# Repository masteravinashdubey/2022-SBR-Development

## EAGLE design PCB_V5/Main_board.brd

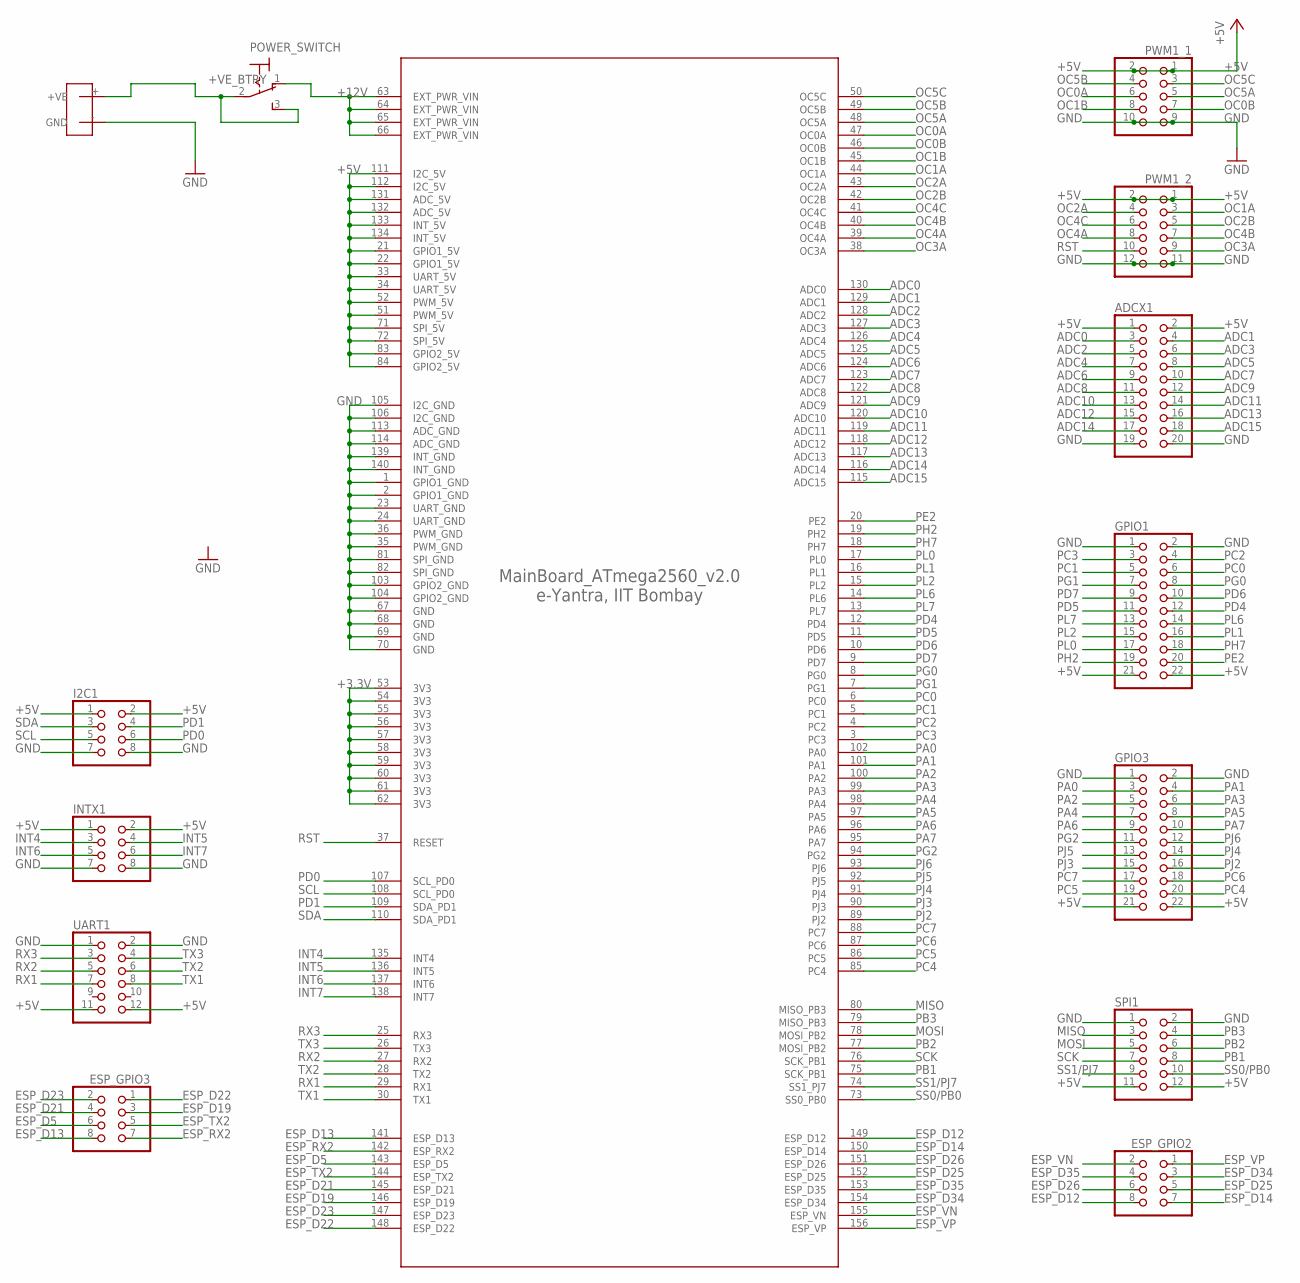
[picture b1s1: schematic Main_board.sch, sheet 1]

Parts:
ADCX1: PINHD-2X10; 2X10
ESP_GPIO2, ESP_GPIO3: PINHD-2X4; 2X04
EYFI_MEGA: ATMEGA2560_V2.0
GPIO1, GPIO3: PINHD-2X11; 2X11
I2C1: PINHD-2X4; 2X04
INTX1: PINHD-2X4; 2X04
POWER_SWITCH: M9040P
PWM1_1: PINHD-2X5; 2X05
PWM1_2: PINHD-2X6; 2X06
SPI1: PINHD-2X6; 2X06
U$1: DEANS
UART1: PINHD-2X6; 2X06

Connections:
+3.3V: EYFI_MEGA.53 (3V3), EYFI_MEGA.54 (3V3), EYFI_MEGA.55 (3V3), EYFI_MEGA.56 (3V3), EYFI_MEGA.57 (3V3), EYFI_MEGA.58 (3V3), EYFI_MEGA.59 (3V3), EYFI_MEGA.60 (3V3), EYFI_MEGA.61 (3V3), EYFI_MEGA.62 (3V3); also elsewhere on the board
+5V: ADCX1.1, ADCX1.2, EYFI_MEGA.21 (GPIO1_5V), EYFI_MEGA.22 (GPIO1_5V), EYFI_MEGA.33 (UART_5V), EYFI_MEGA.34 (UART_5V), EYFI_MEGA.51 (PWM_5V), EYFI_MEGA.52 (PWM_5V), EYFI_MEGA.71 (SPI_5V), EYFI_MEGA.72 (SPI_5V), EYFI_MEGA.83 (GPIO2_5V), EYFI_MEGA.84 (GPIO2_5V), EYFI_MEGA.111 (I2C_5V), EYFI_MEGA.112 (I2C_5V), EYFI_MEGA.131 (ADC_5V), EYFI_MEGA.132 (ADC_5V), EYFI_MEGA.133 (INT_5V), EYFI_MEGA.134 (INT_5V), GPIO1.21, GPIO1.22, GPIO3.21, GPIO3.22, I2C1.1, I2C1.2, INTX1.1, INTX1.2, PWM1_1.1, PWM1_1.2, PWM1_2.1, PWM1_2.2, SPI1.11, SPI1.12, UART1.11, UART1.12; also elsewhere on the board
+12V: EYFI_MEGA.63 (EXT_PWR_VIN), EYFI_MEGA.64 (EXT_PWR_VIN), EYFI_MEGA.65 (EXT_PWR_VIN), EYFI_MEGA.66 (EXT_PWR_VIN), POWER_SWITCH.1 (O); also elsewhere on the board
+VE_BTRY: POWER_SWITCH.2, POWER_SWITCH.3 (S), U$1.+ (+VE)
ADC0: ADCX1.3, EYFI_MEGA.130 (ADC0); also elsewhere on the board
ADC1: ADCX1.4, EYFI_MEGA.129 (ADC1); also elsewhere on the board
ADC2: ADCX1.5, EYFI_MEGA.128 (ADC2); also elsewhere on the board
ADC3: ADCX1.6, EYFI_MEGA.127 (ADC3); also elsewhere on the board
ADC4: ADCX1.7, EYFI_MEGA.126 (ADC4)
ADC5: ADCX1.8, EYFI_MEGA.125 (ADC5)
ADC6: ADCX1.9, EYFI_MEGA.124 (ADC6)
ADC7: ADCX1.10, EYFI_MEGA.123 (ADC7)
ADC8: ADCX1.11, EYFI_MEGA.122 (ADC8)
ADC9: ADCX1.12, EYFI_MEGA.121 (ADC9)
ADC10: ADCX1.13, EYFI_MEGA.120 (ADC10)
ADC11: ADCX1.14, EYFI_MEGA.119 (ADC11)
ADC12: ADCX1.15, EYFI_MEGA.118 (ADC12); also elsewhere on the board
ADC13: ADCX1.16, EYFI_MEGA.117 (ADC13); also elsewhere on the board
ADC14: ADCX1.17, EYFI_MEGA.116 (ADC14); also elsewhere on the board
ADC15: ADCX1.18, EYFI_MEGA.115 (ADC15); also elsewhere on the board
ESP_D5: ESP_GPIO3.6, EYFI_MEGA.143 (ESP_D5)
ESP_D12: ESP_GPIO2.8, EYFI_MEGA.149 (ESP_D12)
ESP_D13: ESP_GPIO3.8, EYFI_MEGA.141 (ESP_D13)
ESP_D14: ESP_GPIO2.7, EYFI_MEGA.150 (ESP_D14)
ESP_D19: ESP_GPIO3.3, EYFI_MEGA.146 (ESP_D19)
ESP_D21: ESP_GPIO3.4, EYFI_MEGA.145 (ESP_D21)
ESP_D22: ESP_GPIO3.1, EYFI_MEGA.148 (ESP_D22)
ESP_D23: ESP_GPIO3.2, EYFI_MEGA.147 (ESP_D23)
ESP_D25: ESP_GPIO2.5, EYFI_MEGA.152 (ESP_D25)
ESP_D26: ESP_GPIO2.6, EYFI_MEGA.151 (ESP_D26)
ESP_D34: ESP_GPIO2.3, EYFI_MEGA.154 (ESP_D34)
ESP_D35: ESP_GPIO2.4, EYFI_MEGA.153 (ESP_D35)
ESP_RX2: ESP_GPIO3.7, EYFI_MEGA.142 (ESP_RX2)
ESP_TX2: ESP_GPIO3.5, EYFI_MEGA.144 (ESP_TX2)
ESP_VN: ESP_GPIO2.2, EYFI_MEGA.155 (ESP_VN)
ESP_VP: ESP_GPIO2.1, EYFI_MEGA.156 (ESP_VP)
GND: ADCX1.19, ADCX1.20, EYFI_MEGA.1 (GPIO1_GND), EYFI_MEGA.2 (GPIO1_GND), EYFI_MEGA.23 (UART_GND), EYFI_MEGA.24 (UART_GND), EYFI_MEGA.35 (PWM_GND), EYFI_MEGA.36 (PWM_GND), EYFI_MEGA.67 (GND), EYFI_MEGA.68 (GND), EYFI_MEGA.69 (GND), EYFI_MEGA.70 (GND), EYFI_MEGA.81 (SPI_GND), EYFI_MEGA.82 (SPI_GND), EYFI_MEGA.103 (GPIO2_GND), EYFI_MEGA.104 (GPIO2_GND), EYFI_MEGA.105 (I2C_GND), EYFI_MEGA.106 (I2C_GND), EYFI_MEGA.113 (ADC_GND), EYFI_MEGA.114 (ADC_GND), EYFI_MEGA.139 (INT_GND), EYFI_MEGA.140 (INT_GND), GPIO1.1, GPIO1.2, GPIO3.1, GPIO3.2, I2C1.7, I2C1.8, INTX1.7, INTX1.8, PWM1_1.9, PWM1_1.10, PWM1_2.11, PWM1_2.12, SPI1.1, SPI1.2, U$1.- (GND), UART1.1, UART1.2; also elsewhere on the board
INT4: EYFI_MEGA.135 (INT4), INTX1.3; also elsewhere on the board
INT5: EYFI_MEGA.136 (INT5), INTX1.4; also elsewhere on the board
INT6: EYFI_MEGA.137 (INT6), INTX1.5; also elsewhere on the board
INT7: EYFI_MEGA.138 (INT7), INTX1.6; also elsewhere on the board
MISO: EYFI_MEGA.80 (MISO_PB3), SPI1.3
MOSI: EYFI_MEGA.78 (MOSI_PB2), SPI1.5
OC0A: EYFI_MEGA.47 (OC0A), PWM1_1.6
OC0B: EYFI_MEGA.46 (OC0B), PWM1_1.7
OC1A: EYFI_MEGA.44 (OC1A), PWM1_2.3
OC1B: EYFI_MEGA.45 (OC1B), PWM1_1.8; also elsewhere on the board
OC2A: EYFI_MEGA.43 (OC2A), PWM1_2.4
OC2B: EYFI_MEGA.42 (OC2B), PWM1_2.5; also elsewhere on the board
OC3A: EYFI_MEGA.38 (OC3A), PWM1_2.9; also elsewhere on the board
OC4A: EYFI_MEGA.39 (OC4A), PWM1_2.8; also elsewhere on the board
OC4B: EYFI_MEGA.40 (OC4B), PWM1_2.7; also elsewhere on the board
OC4C: EYFI_MEGA.41 (OC4C), PWM1_2.6; also elsewhere on the board
OC5A: EYFI_MEGA.48 (OC5A), PWM1_1.5; also elsewhere on the board
OC5B: EYFI_MEGA.49 (OC5B), PWM1_1.4; also elsewhere on the board
OC5C: EYFI_MEGA.50 (OC5C), PWM1_1.3
PA0: EYFI_MEGA.102 (PA0), GPIO3.3; also elsewhere on the board
PA1: EYFI_MEGA.101 (PA1), GPIO3.4; also elsewhere on the board
PA2: EYFI_MEGA.100 (PA2), GPIO3.5; also elsewhere on the board
PA3: EYFI_MEGA.99 (PA3), GPIO3.6; also elsewhere on the board
PA4: EYFI_MEGA.98 (PA4), GPIO3.7; also elsewhere on the board
PA5: EYFI_MEGA.97 (PA5), GPIO3.8; also elsewhere on the board
PA6: EYFI_MEGA.96 (PA6), GPIO3.9; also elsewhere on the board
PA7: EYFI_MEGA.95 (PA7), GPIO3.10; also elsewhere on the board
PB1: EYFI_MEGA.75 (SCK_PB1), SPI1.8
PB2: EYFI_MEGA.77 (MOSI_PB2), SPI1.6
PB3: EYFI_MEGA.79 (MISO_PB3), SPI1.4
PC0: EYFI_MEGA.6 (PC0), GPIO1.6; also elsewhere on the board
PC1: EYFI_MEGA.5 (PC1), GPIO1.5; also elsewhere on the board
PC2: EYFI_MEGA.4 (PC2), GPIO1.4; also elsewhere on the board
PC3: EYFI_MEGA.3 (PC3), GPIO1.3; also elsewhere on the board
PC4: EYFI_MEGA.85 (PC4), GPIO3.20; also elsewhere on the board
PC5: EYFI_MEGA.86 (PC5), GPIO3.19; also elsewhere on the board
PC6: EYFI_MEGA.87 (PC6), GPIO3.18; also elsewhere on the board
PC7: EYFI_MEGA.88 (PC7), GPIO3.17; also elsewhere on the board
PD0: EYFI_MEGA.107 (SCL_PD0), I2C1.6
PD1: EYFI_MEGA.109 (SDA_PD1), I2C1.4
PD4: EYFI_MEGA.12 (PD4), GPIO1.12; also elsewhere on the board
PD5: EYFI_MEGA.11 (PD5), GPIO1.11; also elsewhere on the board
PD6: EYFI_MEGA.10 (PD6), GPIO1.10; also elsewhere on the board
PD7: EYFI_MEGA.9 (PD7), GPIO1.9; also elsewhere on the board
PE2: EYFI_MEGA.20 (PE2), GPIO1.20
PG0: EYFI_MEGA.8 (PG0), GPIO1.8
PG1: EYFI_MEGA.7 (PG1), GPIO1.7
PG2: EYFI_MEGA.94 (PG2), GPIO3.11; also elsewhere on the board
PH2: EYFI_MEGA.19 (PH2), GPIO1.19
PH7: EYFI_MEGA.18 (PH7), GPIO1.18
PJ2: EYFI_MEGA.89 (PJ2), GPIO3.16
PJ3: EYFI_MEGA.90 (PJ3), GPIO3.15
PJ4: EYFI_MEGA.91 (PJ4), GPIO3.14
PJ5: EYFI_MEGA.92 (PJ5), GPIO3.13
PJ6: EYFI_MEGA.93 (PJ6), GPIO3.12; also elsewhere on the board
PL0: EYFI_MEGA.17 (PL0), GPIO1.17
PL1: EYFI_MEGA.16 (PL1), GPIO1.16
PL2: EYFI_MEGA.15 (PL2), GPIO1.15
PL6: EYFI_MEGA.14 (PL6), GPIO1.14
PL7: EYFI_MEGA.13 (PL7), GPIO1.13
RST: EYFI_MEGA.37 (RESET), PWM1_2.10
RX1: EYFI_MEGA.29 (RX1), UART1.7; also elsewhere on the board
RX2: EYFI_MEGA.27 (RX2), UART1.5
RX3: EYFI_MEGA.25 (RX3), UART1.3
SCK: EYFI_MEGA.76 (SCK_PB1), SPI1.7
SCL: EYFI_MEGA.108 (SCL_PD0), I2C1.5; also elsewhere on the board
SDA: EYFI_MEGA.110 (SDA_PD1), I2C1.3; also elsewhere on the board
SS0/PB0: EYFI_MEGA.73 (SS0_PB0), SPI1.10
SS1/PJ7: EYFI_MEGA.74 (SS1_PJ7), SPI1.9
TX1: EYFI_MEGA.30 (TX1), UART1.8
TX2: EYFI_MEGA.28 (TX2), UART1.6
TX3: EYFI_MEGA.26 (TX3), UART1.4

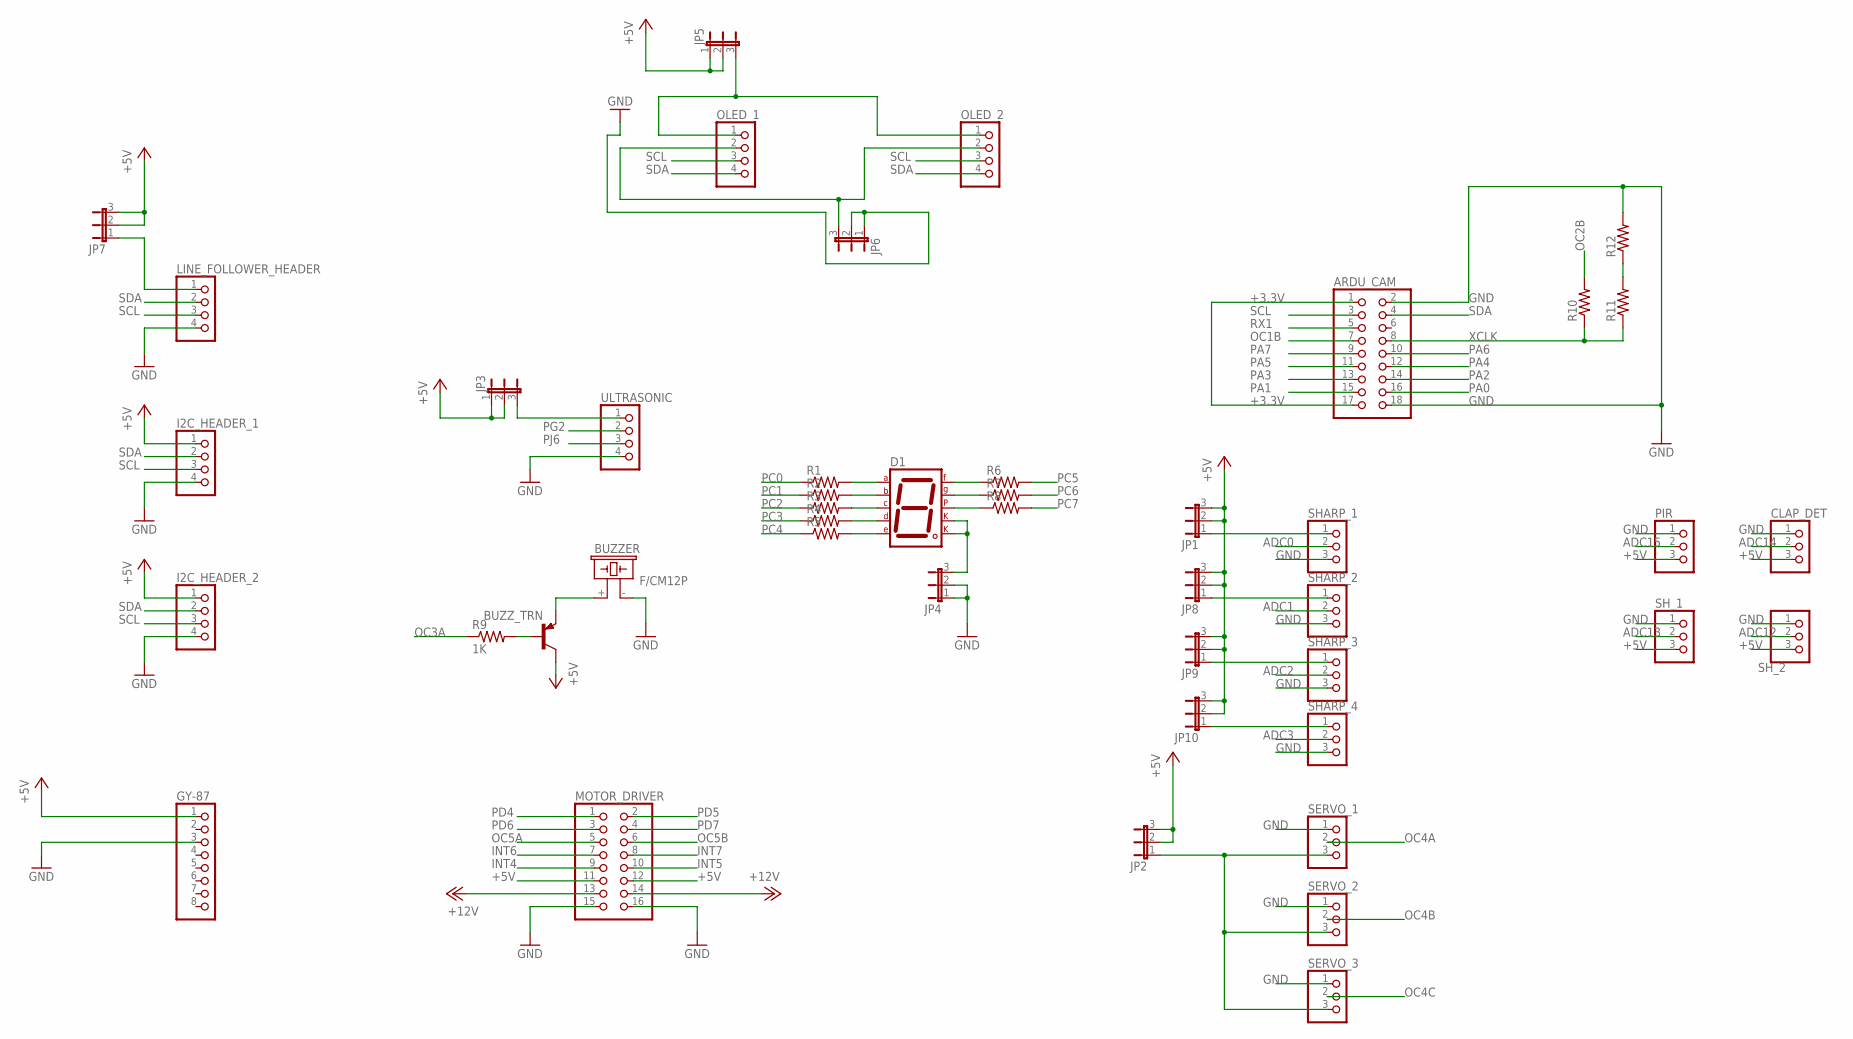
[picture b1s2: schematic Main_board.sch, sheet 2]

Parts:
ARDU_CAM: PINHD-2X9; 2X09
BUZZER: F/CM12P
BUZZ_TRN: BC807-16-PNP-SOT23-BEC; SOT23-BEC
CLAP_DET: PINHD-1X3; 1X03
D1: 7SEG-CK; 7SEG-13
GY-87: PINHD-1X8; 1X08
I2C_HEADER_1, I2C_HEADER_2: PINHD-1X4; 1X04
JP1, JP2, JP3, JP4, JP5, JP6, JP7, JP8, JP9, JP10: JP2E; JP2
LINE_FOLLOWER_HEADER: PINHD-1X4; 1X04
MOTOR_DRIVER: PINHD-2X8; 2X08
OLED_1, OLED_2: PINHD-1X4; 1X04
PIR: PINHD-1X3; 1X03
R1, R2, R3, R4, R5, R6, R7, R8, R10, R11, R12: R-US_R1206; R1206
R9: 1K; R1206
SERVO_1, SERVO_2, SERVO_3: PINHD-1X3; 1X03
SHARP_1, SHARP_2, SHARP_3, SHARP_4: PINHD-1X3; 1X03
SH_1, SH_2: PINHD-1X3; 1X03
ULTRASONIC: PINHD-1X4; 1X04

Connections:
+3.3V: ARDU_CAM.1, ARDU_CAM.17; also elsewhere on the board
+5V: BUZZ_TRN.C, CLAP_DET.3, GY-87.1, I2C_HEADER_1.1, I2C_HEADER_2.1, JP1.2, JP1.3, JP2.2, JP2.3, JP3.1, JP3.2, JP5.1, JP5.2, JP7.2, JP7.3, JP8.2, JP8.3, JP9.2, JP9.3, JP10.2, JP10.3, MOTOR_DRIVER.11, MOTOR_DRIVER.12, PIR.3, SH_1.3, SH_2.3; also elsewhere on the board
+12V: MOTOR_DRIVER.13, MOTOR_DRIVER.14; also elsewhere on the board
ADC0: SHARP_1.2; also elsewhere on the board
ADC1: SHARP_2.2; also elsewhere on the board
ADC2: SHARP_3.2; also elsewhere on the board
ADC3: SHARP_4.2; also elsewhere on the board
ADC12: SH_2.2; also elsewhere on the board
ADC13: SH_1.2; also elsewhere on the board
ADC14: CLAP_DET.2; also elsewhere on the board
ADC15: PIR.2; also elsewhere on the board
GND: ARDU_CAM.2, ARDU_CAM.18, BUZZER.- (2), CLAP_DET.1, GY-87.3, I2C_HEADER_1.4, I2C_HEADER_2.4, JP4.1, JP4.2, JP6.1, JP6.2, LINE_FOLLOWER_HEADER.4, MOTOR_DRIVER.15, MOTOR_DRIVER.16, PIR.1, R12.2, SERVO_1.1, SERVO_2.1, SERVO_3.1, SHARP_1.3, SHARP_2.3, SHARP_3.3, SHARP_4.3, SH_1.1, SH_2.1, ULTRASONIC.4; also elsewhere on the board
INT4: MOTOR_DRIVER.9; also elsewhere on the board
INT5: MOTOR_DRIVER.10; also elsewhere on the board
INT6: MOTOR_DRIVER.7; also elsewhere on the board
INT7: MOTOR_DRIVER.8; also elsewhere on the board
unnamed: JP1.1, SHARP_1.1
unnamed: D1.7 (A), R1.2
unnamed: BUZZER.+ (1), BUZZ_TRN.E
unnamed: D1.6 (B), R2.2
unnamed: BUZZ_TRN.B, R9.2
unnamed: D1.4 (C), R3.2
unnamed: D1.2 (D), R4.2
unnamed: D1.1 (E), R5.2
unnamed: D1.9 (F), R6.1
unnamed: D1.10 (G), R7.1
unnamed: D1.5 (DP), R8.1
unnamed: JP3.3, ULTRASONIC.1
unnamed: D1.3 (CK1), D1.8 (CK2), JP4.3
unnamed: JP5.3, OLED_1.1, OLED_2.1
unnamed: JP6.3, OLED_1.2, OLED_2.2
unnamed: JP7.1, LINE_FOLLOWER_HEADER.1
unnamed: R11.2, R12.1
unnamed: JP8.1, SHARP_2.1
unnamed: JP10.1, SHARP_4.1
unnamed: JP9.1, SHARP_3.1
unnamed: JP2.1, SERVO_1.3, SERVO_2.3, SERVO_3.3
OC1B: ARDU_CAM.7; also elsewhere on the board
OC2B: R10.2; also elsewhere on the board
OC3A: R9.1; also elsewhere on the board
OC4A: SERVO_1.2; also elsewhere on the board
OC4B: SERVO_2.2; also elsewhere on the board
OC4C: SERVO_3.2; also elsewhere on the board
OC5A: MOTOR_DRIVER.5; also elsewhere on the board
OC5B: MOTOR_DRIVER.6; also elsewhere on the board
PA0: ARDU_CAM.16; also elsewhere on the board
PA1: ARDU_CAM.15; also elsewhere on the board
PA2: ARDU_CAM.14; also elsewhere on the board
PA3: ARDU_CAM.13; also elsewhere on the board
PA4: ARDU_CAM.12; also elsewhere on the board
PA5: ARDU_CAM.11; also elsewhere on the board
PA6: ARDU_CAM.10; also elsewhere on the board
PA7: ARDU_CAM.9; also elsewhere on the board
PC0: R1.1; also elsewhere on the board
PC1: R2.1; also elsewhere on the board
PC2: R3.1; also elsewhere on the board
PC3: R4.1; also elsewhere on the board
PC4: R5.1; also elsewhere on the board
PC5: R6.2; also elsewhere on the board
PC6: R7.2; also elsewhere on the board
PC7: R8.2; also elsewhere on the board
PD4: MOTOR_DRIVER.1; also elsewhere on the board
PD5: MOTOR_DRIVER.2; also elsewhere on the board
PD6: MOTOR_DRIVER.3; also elsewhere on the board
PD7: MOTOR_DRIVER.4; also elsewhere on the board
PG2: ULTRASONIC.2; also elsewhere on the board
PJ6: ULTRASONIC.3; also elsewhere on the board
RX1: ARDU_CAM.5; also elsewhere on the board
SCL: ARDU_CAM.3, I2C_HEADER_1.3, I2C_HEADER_2.3, LINE_FOLLOWER_HEADER.3, OLED_1.3, OLED_2.3; also elsewhere on the board
SDA: ARDU_CAM.4, I2C_HEADER_1.2, I2C_HEADER_2.2, LINE_FOLLOWER_HEADER.2, OLED_1.4, OLED_2.4; also elsewhere on the board
XCLK: ARDU_CAM.8, R10.1, R11.1

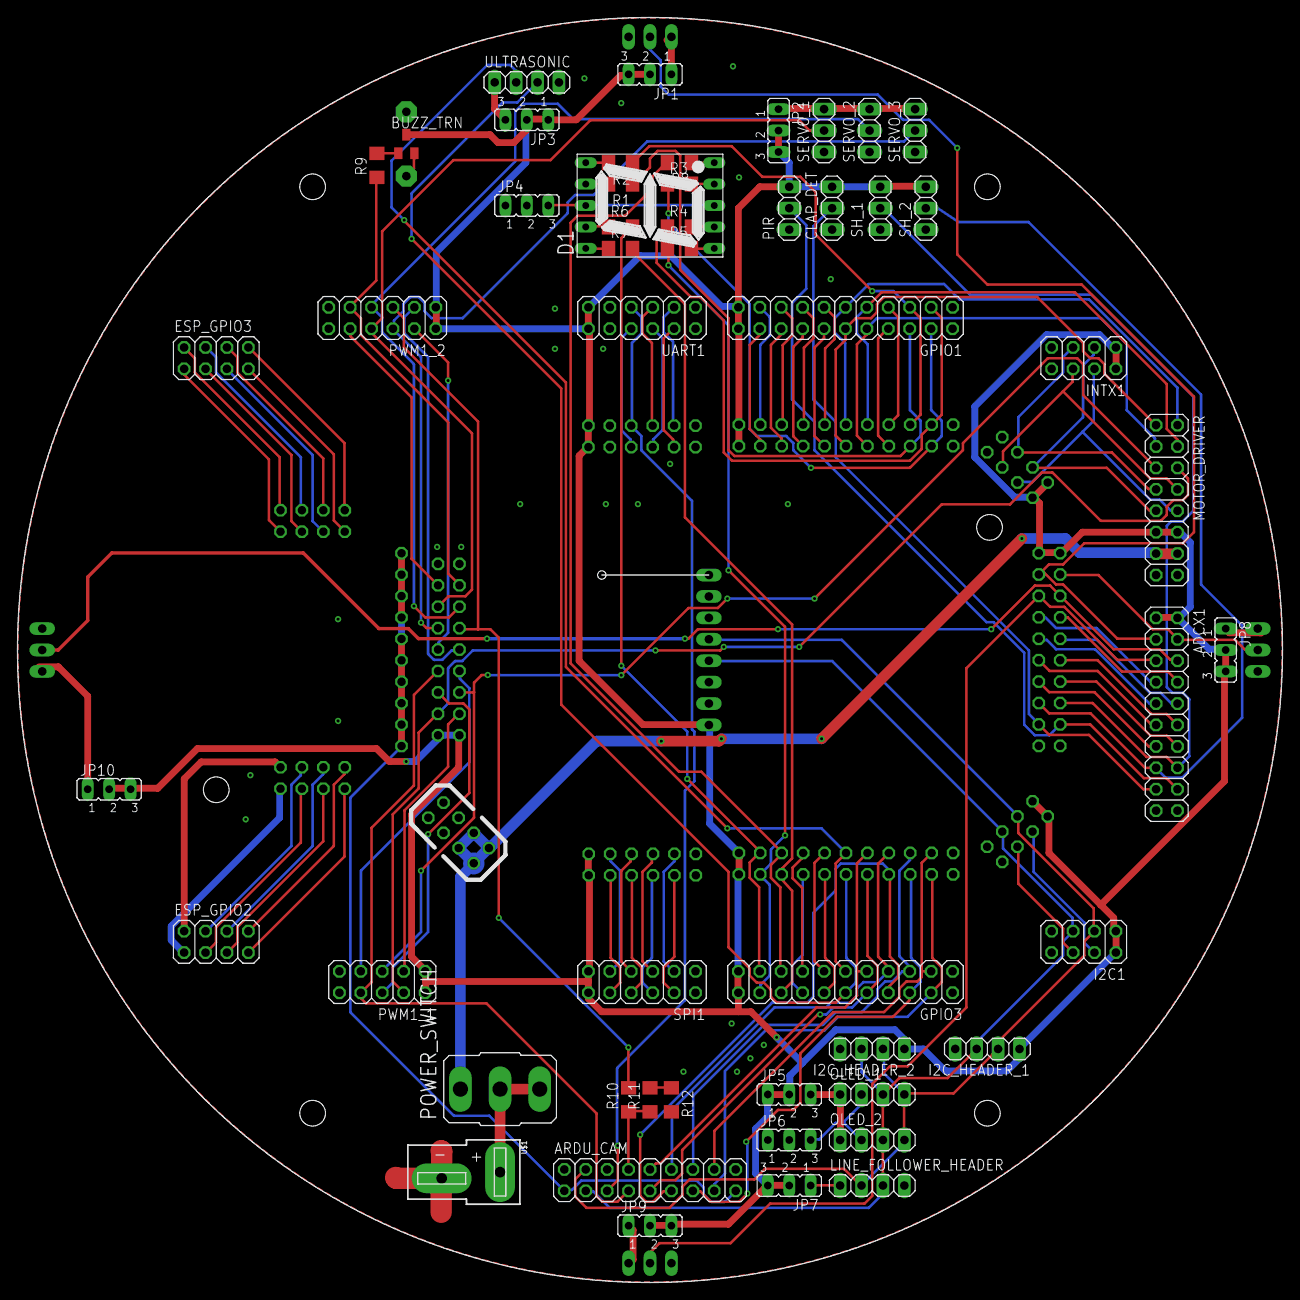
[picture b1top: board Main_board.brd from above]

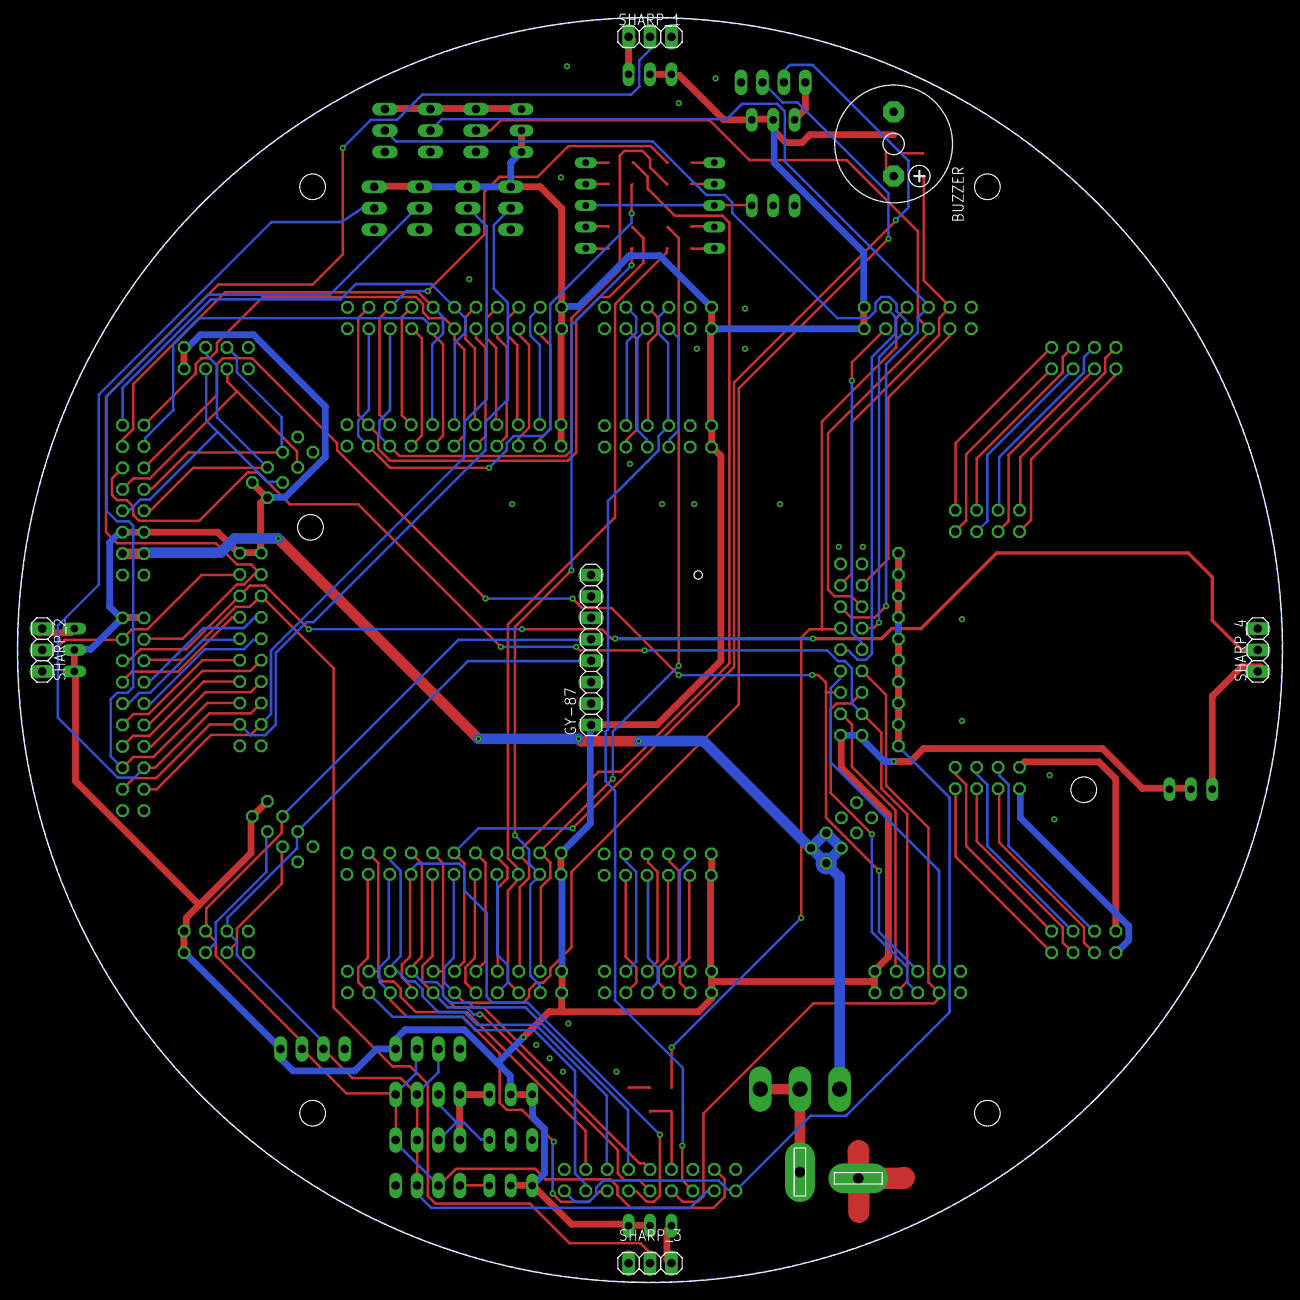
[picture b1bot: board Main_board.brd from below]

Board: 2 copper layers, 150.0 x 150.0 mm, 59 parts (6 on the bottom side), 131 nets.

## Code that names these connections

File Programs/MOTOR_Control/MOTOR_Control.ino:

// These constants won't change. They're used to give names to the pins used:
//const int lowestPin = 2;
//const int highestPin = 13;

#define RM1 PD4
#define RM2 PD7
#define LM1 PD5
#define LM2 PD6

#define PWM_RM PL3
#define PWM_LM PL4

void setup() {
  // set pins 2 through 13 as outputs:
  //for (int thisPin = lowestPin; thisPin <= highestPin; thisPin++) {
    pinMode(RM1, OUTPUT);
    pinMode(RM2, OUTPUT);
    pinMode(LM1, OUTPUT);
    pinMode(LM2, OUTPUT);
    pinMode(PL3, OUTPUT);
    pinMode(PL4, OUTPUT);
    analogWrite(PWM_RM, 80);
    analogWrite(PWM_LM, 80);
//     digitalWrite(PWM_RM, HIGH);
//     digitalWrite(PWM_LM, HIGH);
  //}
}

void loop() {
  digitalWrite(RM1, HIGH);
  digitalWrite(LM1, HIGH);
  digitalWrite(RM2, LOW);
  digitalWrite(LM2, LOW);
  delay(5000);
  digitalWrite(RM1, LOW);
  digitalWrite(LM1, LOW);
  digitalWrite(RM2, HIGH);
  digitalWrite(LM2, HIGH);
  delay(5000);
  
}

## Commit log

2023-12-04 First
2023-12-04 2nd Commit
2023-12-04 3rd commit
2023-12-04 cad commit
